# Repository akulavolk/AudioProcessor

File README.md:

Volume/tone control board based on the TDA7439 audio processor chip and [ahuxtable's Arduino library](https://github.com/ahuxtable/TDA7439).

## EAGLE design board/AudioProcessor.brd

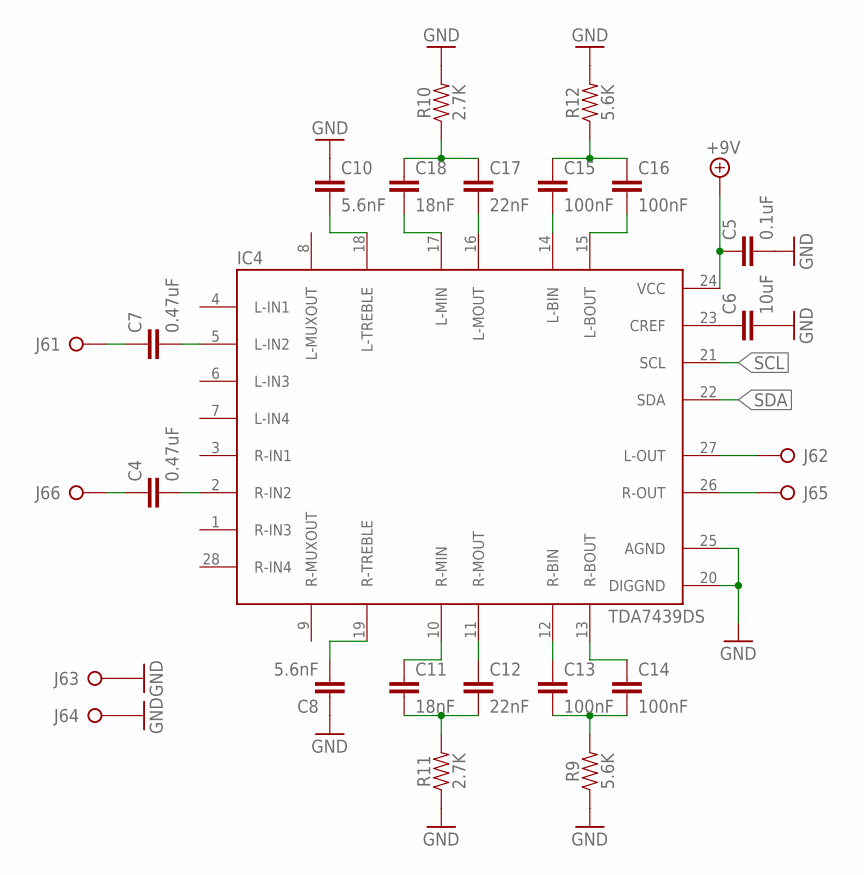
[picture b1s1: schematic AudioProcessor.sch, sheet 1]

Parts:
C4, C7: 0.47uF; CAPACITOR-5MM
C5: 0.1uF; CAPACITOR-0603
C6: 10uF; CAPACITOR-1206
C8, C10: 5.6nF; CAPACITOR-5MM
C11, C18: 18nF; CAPACITOR-5MM
C12, C17: 22nF; CAPACITOR-5MM
C13, C14, C15, C16: 100nF; CAPACITOR-5MM
IC4: TDA7439DS; SO-28W
J6: PINHD-1X6-JST-PH; JST-B6B-PH
R9, R12: 5.6K; RESISTOR-0805
R10, R11: 2.7K; RESISTOR-0805

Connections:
+9V: C5.1, IC4.24 (VCC); also elsewhere on the board
GND: C5.2, C6.2, C8.1, C10.1, IC4.20 (DIGGND), IC4.25 (AGND), J6.3, J6.4, R9.1, R10.2, R11.1, R12.2; also elsewhere on the board
L-IN: C7.2, IC4.5 (L-IN2)
L-IN-RAW: C7.1, J6.1
L-OUT: IC4.27 (L-OUT), J6.2
unnamed: C10.2, IC4.18 (L-TREBLE)
unnamed: C18.2, IC4.17 (L-MIN)
unnamed: C17.2, IC4.16 (L-MOUT)
unnamed: C17.1, C18.1, R10.1
unnamed: C15.2, IC4.14 (L-BIN)
unnamed: C16.2, IC4.15 (L-BOUT)
unnamed: C15.1, C16.1, R12.1
unnamed: C8.2, IC4.19 (R-TREBLE)
unnamed: C11.1, IC4.10 (R-MIN)
unnamed: C12.1, IC4.11 (R-MOUT)
unnamed: C11.2, C12.2, R11.2
unnamed: C13.2, C14.2, R9.2
unnamed: C14.1, IC4.13 (R-BOUT)
unnamed: C13.1, IC4.12 (R-BIN)
unnamed: C6.1, IC4.23 (CREF)
R-IN: C4.2, IC4.2 (R-IN2)
R-IN-RAW: C4.1, J6.6
R-OUT: IC4.26 (R-OUT), J6.5
SCL: IC4.21 (SCL); also elsewhere on the board
SDA: IC4.22 (SDA); also elsewhere on the board

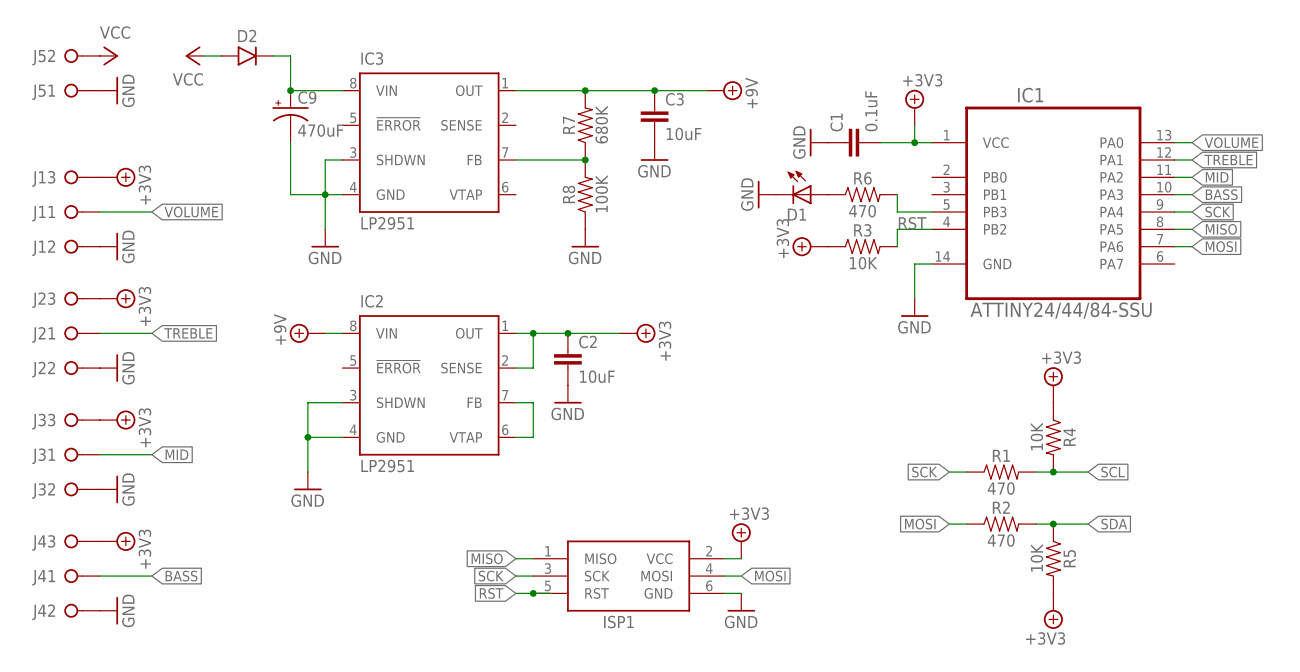
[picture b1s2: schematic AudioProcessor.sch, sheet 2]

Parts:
C1: 0.1uF; CAPACITOR-0603
C2, C3: 10uF; CAPACITOR-1206
C9: 470uF; CAP-POL-3.5-8
D1: LED-0805
D2: DIODE-DO214AC; DO-214AC
IC1: ATTINY24/44/84-SSU; SO-14
IC2, IC3: LP2951; SOIC-08
ISP1: ICSP-HEADER-6; ICSP-HEADER
J1, J2, J3, J4: PINHD-1X3-JST-PH; JST-B3B-PH
J5: PINHD-1X2-JST-PH; JST-B2B-PH
R1, R2, R6: 470; RESISTOR-0805
R3, R4, R5: 10K; RESISTOR-0805
R7: 680K; RESISTOR-0805
R8: 100K; RESISTOR-0805

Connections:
+3V3: C1.2, C2.1, IC1.1 (VCC), IC2.1 (OUT), IC2.2 (SENSE), ISP1.2 (VCC), J1.3, J2.3, J3.3, J4.3, R3.1, R4.1, R5.2
+9V: C3.1, IC2.8 (VIN), IC3.1 (OUT), R7.2; also elsewhere on the board
BASS: IC1.10 (PA3), J4.1
GND: C1.1, C2.2, C3.2, C9.-, D1.2 (C), IC1.14 (GND), IC2.3 (SHDWN), IC2.4 (GND), IC3.3 (SHDWN), IC3.4 (GND), ISP1.6 (GND), J1.2, J2.2, J3.2, J4.2, J5.1, R8.1; also elsewhere on the board
LED: IC1.5 (PB3), R6.2
MID: IC1.11 (PA2), J3.1
MISO: IC1.8 (PA5), ISP1.1 (MISO)
MOSI: IC1.7 (PA6), ISP1.4 (MOSI), R2.1
unnamed: D1.1 (A), R6.1
unnamed: IC3.7 (FB), R7.1, R8.2
unnamed: C9.+, D2.2 (-), IC3.8 (VIN)
unnamed: IC2.6 (VTAP), IC2.7 (FB)
RST: IC1.4 (PB2), ISP1.5 (RST), R3.2
SCK: IC1.9 (PA4), ISP1.3 (SCK), R1.1
SCL: R1.2, R4.2; also elsewhere on the board
SDA: R2.2, R5.1; also elsewhere on the board
TREBLE: IC1.12 (PA1), J2.1
VCC: D2.1 (+), J5.2
VOLUME: IC1.13 (PA0), J1.1

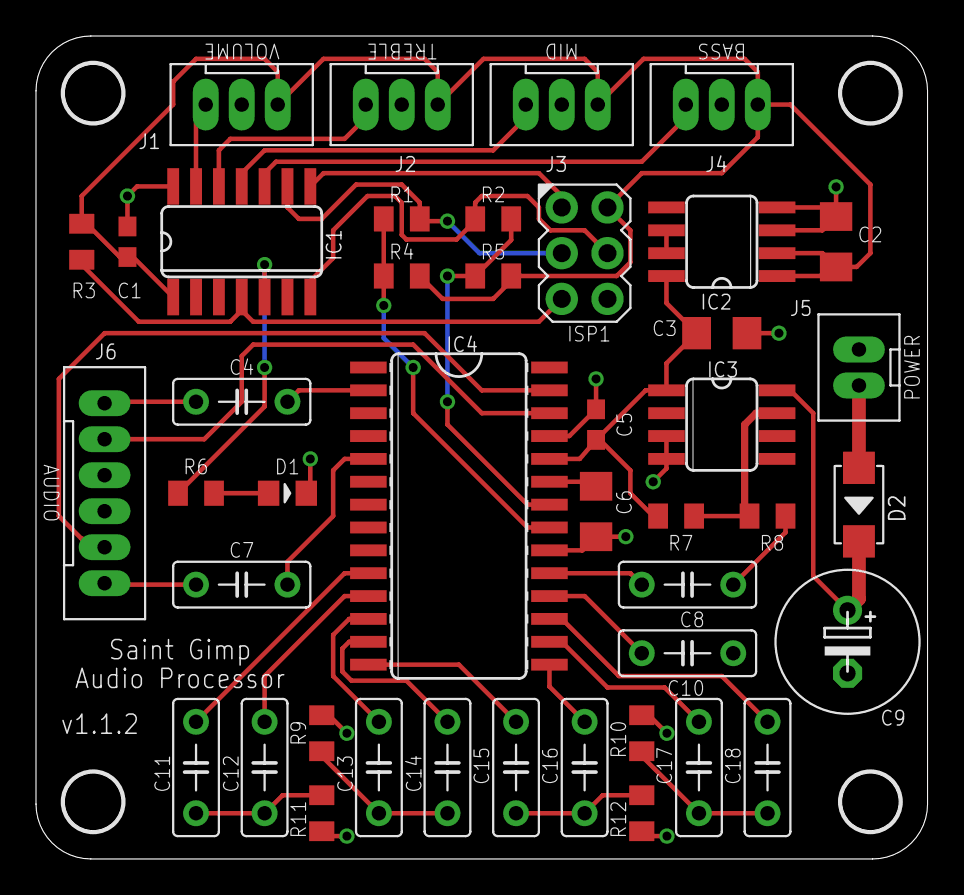
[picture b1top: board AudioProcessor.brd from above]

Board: 2 copper layers, 49.5 x 45.7 mm, 47 parts (0 on the bottom side), 40 nets.

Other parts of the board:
U$1, U$2, U$3, U$4: MOUNTING-HOLE-3.2MM

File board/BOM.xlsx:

Table 1
Qty | Value | Device | Package | Parts | Description | MPN | Notes
1 |  | DIODE-DO214AC | DO-214AC | D2 |  | MF-DIO-SMA-B140
2 | 0.1uF | CAPACITOR-0603 | CAPACITOR-0603 | C1, C5 | Ceramic Capacitor | MF-CAP-0603-0.1uF
2 | 0.47uF | CAPACITOR-5MM | CAPACITOR-5MM | C4, C7 | Film Capacitor | B32529C474J | This should be B32529C0474J289 but this is what returns an available result in 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
1 | 100K | RESISTOR-0805 | RESISTOR-0805 | R8 |  | MF-RES-0805-100K
4 | 100nF | CAPACITOR-5MM | CAPACITOR-5MM | C13, C14, C15, C16 | Film Capacitor | B32529C0104J289 | This should be B32529C0104J289 but we use the mangled part number so Macrofab c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
3 | 10K | RESISTOR-0805 | RESISTOR-0805 | R3, R4, R5 |  | MF-RES-0805-10K
3 | 10uF | CAPACITOR-1206 | CAPACITOR-1206 | C2, C3, C6 | Ceramic Capacitor | MF-CAP-1206-10uF
2 | 18nF | CAPACITOR-5MM | CAPACITOR-5MM | C11, C18 | Film Capacitor | B32529C0183J289 | Suffix 000 is bulk packaging
2 | 2.7K | RESISTOR-0805 | RESISTOR-0805 | R10, R11 |  | RC0805FR-072K7L
2 | 22nF | CAPACITOR-5MM | CAPACITOR-5MM | C12, C17 | Film Capacitor | B32529C0223J289 | Suffix 000 is bulk packaging
3 | 470 | RESISTOR-0805 | RESISTOR-0805 | R1, R2, R6 |  | MF-RES-0805-470
1 | 470uF | CAPACITOR-POLARIZED-3.5-8 | CAP-POL-3.5-8 | C9 | Polarized Capacitor | 16YXJ470M8X11.5
2 | 5.6K | RESISTOR-0805 | RESISTOR-0805 | R9, R12 |  | MF-RES-0805-5.6K
2 | 5.6nF | CAPACITOR-5MM | CAPACITOR-5MM | C8, C10 | Film Capacitor | B32529C0562J289 | Suffix 000 is bulk packaging
1 | 680K | RESISTOR-0805 | RESISTOR-0805 | R7 |  | MF-RES-0805-680K
1 | ATTINY24/44/84-SSU | ATTINY24/44/84-SSU | SO-14 | IC1 | 8-bit Microcontroller with In-System Programmable Flash | ATTINY84A-SSU
1 | ICSP-HEADER-6 | ICSP-HEADER-6 | ICSP-HEADER | ISP1 | ICSP HEADER
1 | LED-0805 | LED-0805 | LED-0805 | D1 |  | MF-LED-0805-RED
2 | LP2951 | LP2951 | SOIC-08 | IC2, IC3 |  | LP2951-33DR
4 | PINHD-1X3-JST-PH | PINHD-1X3-JST-PH | JST-B3B-PH | J1, J2, J3, J4 | PIN HEADER | B3B-PH-K-S(LF)(SN)
1 | PINHD-1X2-JST-PH | PINHD-1X2-JST-PH | JST-B3B-PH | J5 | PIN HEADER | B2B-PH-K-S(LF)(SN)
1 | PINHD-1X6-JST-PH | PINHD-1X6-JST-PH | JST-B6B-PH | J6 |  | B6B-PH-K-S(LF)(SN)
1 | TDA7439DS | TDA7439DS | SO-28W | IC4 |  | TDA7439DS13TR

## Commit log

2016-11-15 Move code files because Arduino IDE is silly
2017-02-03 V1 plus a few in-progress modifications
2017-02-03 Removed unnecessary output biasing
2017-03-03 Add status LED and other improvements
2017-09-09 Add comment about MCU targeting
2017-09-09 Change regulator programming resistor to a value that matches house part availability and still gives us an acceptable output voltage.
2017-10-25 Update with library changes and tune for Macrofab house parts
2017-10-25 Add BOM document
2017-10-26 Move silkscreen text to the correct layers, and update BOM
2017-10-27 Fix JST header orientation
2018-02-14 Board updates for manufacturing
2018-02-14 Add targeting notes and flags to configure usage of input controls
2018-02-14 Use attenuation to smooth out the lower volume ramp
2018-02-14 Avoid headaches when flashing an operating system
2018-02-14 Better headache avoidance
